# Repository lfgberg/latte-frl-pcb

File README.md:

# This has not yet been tested, and firmware has not yet been pushed to qmk/via, pcb may or may not function as intended

# Latte FRL PCB

PCB designed for Keyboard Cafe's Latte FRL WKL TKL keyboard. PCB art by the wonderful [Stellaidescope](https://twitter.com/stellaidoscope).

## Renders

## Layout

## Production

Download the [latest release of the production files](https://github.com/lfgberg/latte-frl-pcb/releases), and submit them to a PCB manufacturer like JLCPCB or PCBWay.

## Author
[Lfgberg](https://github.com/lfgberg)
<br>

## License
[Attribution-NonCommercial-ShareAlike 4.0 International](https://creativecommons.org/licenses/by-nc-sa/4.0/)

This is not available for commercial use, contact [Lfgberg](https://github.com/lfgberg) for more information.

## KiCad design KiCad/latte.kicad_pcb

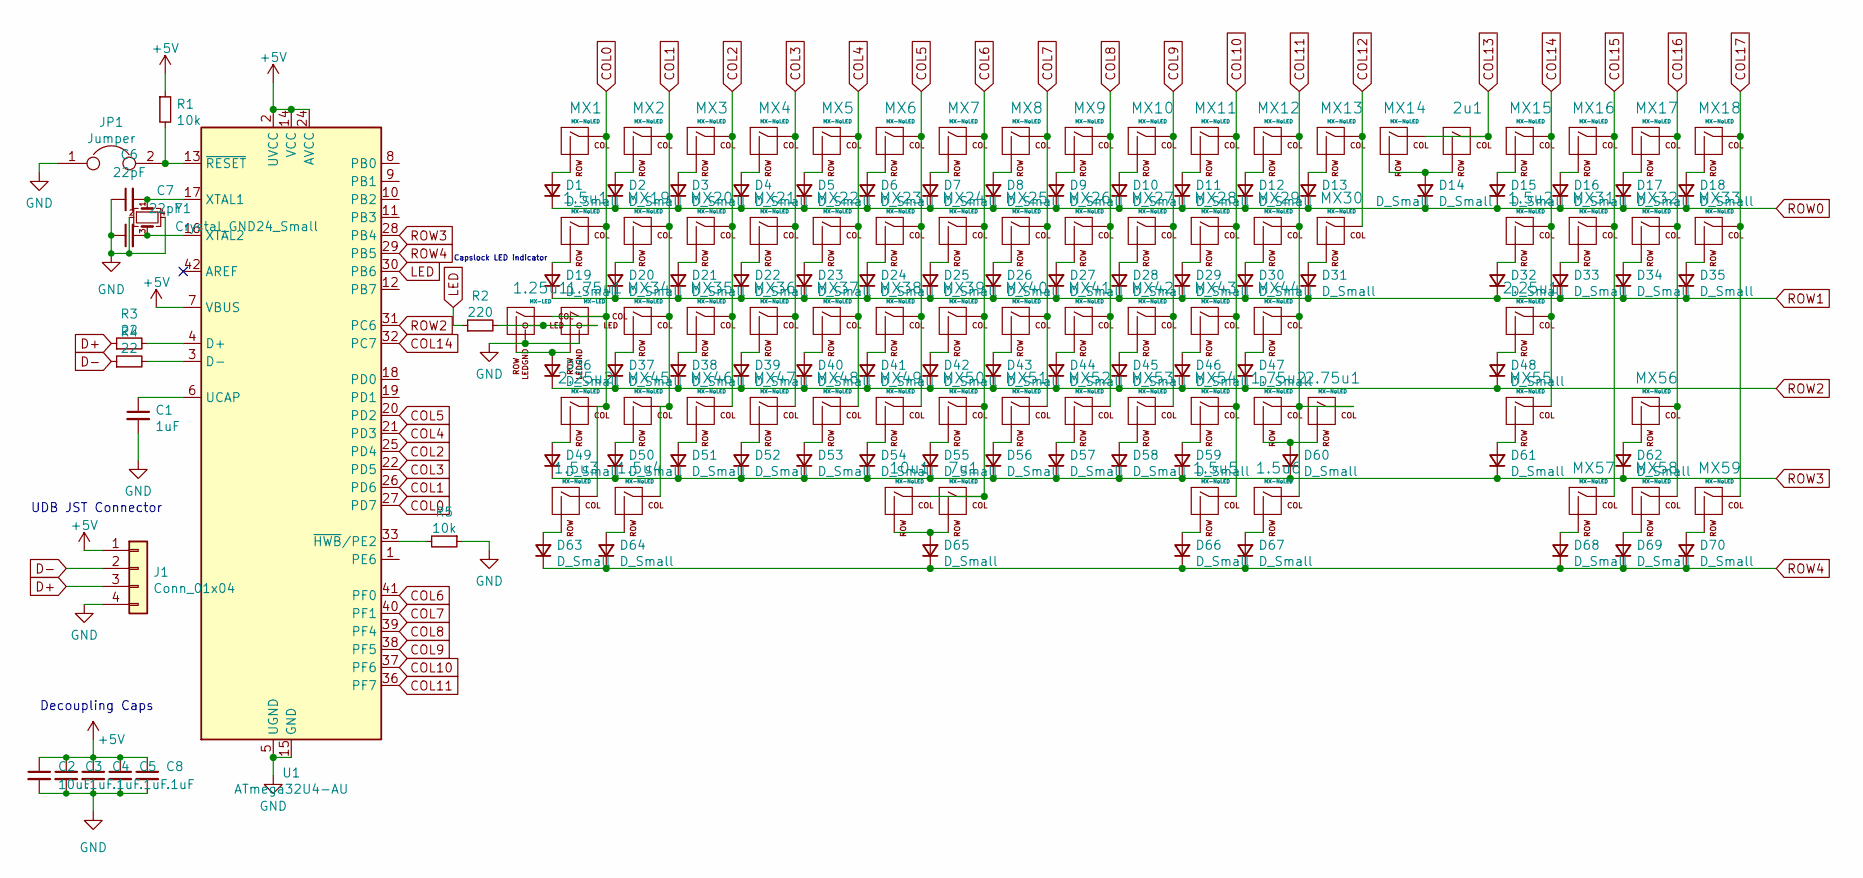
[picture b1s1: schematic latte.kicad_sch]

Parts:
1.5u1, 1.5u2, 1.5u3, 1.5u4, 1.5u5, 1.5u6: MX-NoLED; MXOnly-1.5U-NoLED
1.25u1: MX-LED; MXOnly-1.25U
1.75u1: MX-LED; MXOnly-1.75U
1.75u2: MX-NoLED; MXOnly-1.75U-NoLED
2.25u1, 2.25u2: MX-NoLED; MXOnly-2.25U-NoLED
2.75u1: MX-NoLED; MXOnly-2.75U-NoLED
2u1: MXOnly-2U-NoLED
7u1: MX-NoLED; MXOnly-7U-ReversedStabilizers-NoLED
10u1: MX-NoLED; MX-8U-NoSwitch
C1: 1uF; C_0805_2012Metric
C2: 10uF; C_0805_2012Metric
C3, C4, C5, C8: .1uF; C_0805_2012Metric
C6, C7: 22pF; C_0805_2012Metric
D1, D2, D3, D4, D5, D6, D7, D8, D9, D10, D11, D12, D13, D14, D15, D16, D17, D18, D19, D20, D21, D22, D23, D24, D25, D26, D27, D28, D29, D30, D31, D32, D33, D34, D35, D36, D37, D38, D39, D40, D41, D42, D43, D44, D45, D46, D47, D48, D49, D50, D51, D52, D53, D54, D55, D56, D57, D58, D59, D60, D61, D62, D63, D64, D65, D66, D67, D68, D69, D70: D_Small; D_SOD-123-Pretty
J1: Conn_01x04; JST-SR-4
JP1: Jumper; ResetJumper
MX1, MX2, MX3, MX4, MX5, MX6, MX7, MX8, MX9, MX10, MX11, MX12, MX13, MX14, MX15, MX16, MX17, MX18, MX19, MX20, MX21, MX22, MX23, MX24, MX25, MX26, MX27, MX28, MX29, MX30, MX31, MX32, MX33, MX34, MX35, MX36, MX37, MX38, MX39, MX40, MX41, MX42, MX43, MX44, MX45, MX46, MX47, MX48, MX49, MX50, MX51, MX52, MX53, MX54, MX55, MX56, MX57, MX58, MX59: MX-NoLED; MXOnly-1U-NoLED
R1, R5: 10k; R_0805_2012Metric
R2: 220; R_0805_2012Metric
R3, R4: 22; R_0805_2012Metric
U1: ATmega32U4-AU; QFN_TQFP-44_Combined
Y1: Crystal_GND24_Small; Crystal_SMD_3225-4Pin_3.2x2.5mm_HandSoldering

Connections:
+5V: C2.1, C3.1, C4.1, C5.1, C8.1, J1.1, R1.1, U1.2 (UVCC), U1.7 (VBUS), U1.14 (VCC), U1.24 (AVCC), U1.34 (VCC), U1.44 (AVCC)
COL0: 1.5u1.1 (COL), 1.5u3.1 (COL), 1.25u1.1 (COL), 1.75u1.1 (COL), 2.25u2.1 (COL), MX1.1 (COL), U1.27 (PD7)
COL1: 1.5u4.1 (COL), MX2.1 (COL), MX19.1 (COL), MX34.1 (COL), MX45.1 (COL), U1.26 (PD6)
COL2: MX3.1 (COL), MX20.1 (COL), MX35.1 (COL), MX46.1 (COL), U1.25 (PD4)
COL3: MX4.1 (COL), MX21.1 (COL), MX36.1 (COL), MX47.1 (COL), U1.22 (PD5)
COL4: MX5.1 (COL), MX22.1 (COL), MX37.1 (COL), MX48.1 (COL), U1.21 (PD3)
COL5: MX6.1 (COL), MX23.1 (COL), MX38.1 (COL), MX49.1 (COL), U1.20 (PD2)
COL6: 7u1.1 (COL), 10u1.1 (COL), MX7.1 (COL), MX24.1 (COL), MX39.1 (COL), MX50.1 (COL), U1.41 (PF0)
COL7: MX8.1 (COL), MX25.1 (COL), MX40.1 (COL), MX51.1 (COL), U1.40 (PF1)
COL8: MX9.1 (COL), MX26.1 (COL), MX41.1 (COL), MX52.1 (COL), U1.39 (PF4)
COL9: MX10.1 (COL), MX27.1 (COL), MX42.1 (COL), MX53.1 (COL), U1.38 (PF5)
COL10: 1.5u5.1 (COL), MX11.1 (COL), MX28.1 (COL), MX43.1 (COL), MX54.1 (COL), U1.37 (PF6)
COL11: 1.5u6.1 (COL), 1.75u2.1 (COL), 2.75u1.1 (COL), MX12.1 (COL), MX29.1 (COL), MX44.1 (COL), U1.36 (PF7)
COL12: MX13.1 (COL), MX30.1 (COL)
COL13: 2u1.1 (COL), MX14.1 (COL)
COL14: 1.5u2.1 (COL), 2.25u1.1 (COL), MX15.1 (COL), MX55.1 (COL), U1.32 (PC7)
COL15: MX16.1 (COL), MX31.1 (COL), MX57.1 (COL)
COL16: MX17.1 (COL), MX32.1 (COL), MX56.1 (COL), MX58.1 (COL)
COL17: MX18.1 (COL), MX33.1 (COL), MX59.1 (COL)
D+: J1.3, R3.1
D-: J1.2, R4.1
GND: 1.25u1.4 (LEDGND), 1.75u1.4 (LEDGND), C1.2, C2.2, C3.2, C4.2, C5.2, C6.1, C7.1, C8.2, J1.4, JP1.1, R5.1, U1.5 (UGND), U1.15 (GND), U1.23 (GND), U1.35 (GND), U1.43 (GND), Y1.2, Y1.4
LED: R2.1, U1.30 (PB6)
unnamed: 1.5u1.2 (ROW), D19.2 (A)
unnamed: 1.5u2.2 (ROW), D32.2 (A)
unnamed: 1.5u3.2 (ROW), D63.2 (A)
unnamed: 1.5u4.2 (ROW), D64.2 (A)
unnamed: 1.5u5.2 (ROW), D66.2 (A)
unnamed: 1.5u6.2 (ROW), D67.2 (A)
unnamed: 1.25u1.2 (ROW), 1.75u1.2 (ROW), D36.2 (A)
unnamed: 1.25u1.3 (LED), 1.75u1.3 (LED), R2.2
unnamed: 1.75u2.2 (ROW), 2.75u1.2 (ROW), D60.2 (A)
unnamed: 2.25u1.2 (ROW), D48.2 (A)
unnamed: 2.25u2.2 (ROW), D49.2 (A)
unnamed: 2u1.2 (ROW), D14.2 (A), MX14.2 (ROW)
unnamed: 7u1.2 (ROW), 10u1.2 (ROW), D65.2 (A)
unnamed: C1.1, U1.6 (UCAP)
unnamed: C6.2, U1.17 (XTAL1), Y1.1
unnamed: C7.2, U1.16 (XTAL2), Y1.3
unnamed: D1.2 (A), MX1.2 (ROW)
unnamed: D2.2 (A), MX2.2 (ROW)
unnamed: D3.2 (A), MX3.2 (ROW)
unnamed: D4.2 (A), MX4.2 (ROW)
unnamed: D5.2 (A), MX5.2 (ROW)
unnamed: D6.2 (A), MX6.2 (ROW)
unnamed: D7.2 (A), MX7.2 (ROW)
unnamed: D8.2 (A), MX8.2 (ROW)
unnamed: D9.2 (A), MX9.2 (ROW)
unnamed: D10.2 (A), MX10.2 (ROW)
unnamed: D11.2 (A), MX11.2 (ROW)
unnamed: D12.2 (A), MX12.2 (ROW)
unnamed: D13.2 (A), MX13.2 (ROW)
unnamed: D15.2 (A), MX15.2 (ROW)
unnamed: D16.2 (A), MX16.2 (ROW)
unnamed: D17.2 (A), MX17.2 (ROW)
unnamed: D18.2 (A), MX18.2 (ROW)
unnamed: D20.2 (A), MX19.2 (ROW)
unnamed: D21.2 (A), MX20.2 (ROW)
unnamed: D22.2 (A), MX21.2 (ROW)
unnamed: D23.2 (A), MX22.2 (ROW)
unnamed: D24.2 (A), MX23.2 (ROW)
unnamed: D25.2 (A), MX24.2 (ROW)
unnamed: D26.2 (A), MX25.2 (ROW)
unnamed: D27.2 (A), MX26.2 (ROW)
unnamed: D28.2 (A), MX27.2 (ROW)
unnamed: D29.2 (A), MX28.2 (ROW)
unnamed: D30.2 (A), MX29.2 (ROW)
unnamed: D31.2 (A), MX30.2 (ROW)
unnamed: D33.2 (A), MX31.2 (ROW)
unnamed: D34.2 (A), MX32.2 (ROW)
unnamed: D35.2 (A), MX33.2 (ROW)
unnamed: D37.2 (A), MX34.2 (ROW)
unnamed: D38.2 (A), MX35.2 (ROW)
unnamed: D39.2 (A), MX36.2 (ROW)
unnamed: D40.2 (A), MX37.2 (ROW)
unnamed: D41.2 (A), MX38.2 (ROW)
unnamed: D42.2 (A), MX39.2 (ROW)
unnamed: D43.2 (A), MX40.2 (ROW)
unnamed: D44.2 (A), MX41.2 (ROW)
unnamed: D45.2 (A), MX42.2 (ROW)
unnamed: D46.2 (A), MX43.2 (ROW)
unnamed: D47.2 (A), MX44.2 (ROW)
unnamed: D50.2 (A), MX45.2 (ROW)
unnamed: D51.2 (A), MX46.2 (ROW)
unnamed: D52.2 (A), MX47.2 (ROW)
unnamed: D53.2 (A), MX48.2 (ROW)
unnamed: D54.2 (A), MX49.2 (ROW)
unnamed: D55.2 (A), MX50.2 (ROW)
unnamed: D56.2 (A), MX51.2 (ROW)
unnamed: D57.2 (A), MX52.2 (ROW)
unnamed: D58.2 (A), MX53.2 (ROW)
unnamed: D59.2 (A), MX54.2 (ROW)
unnamed: D61.2 (A), MX55.2 (ROW)
unnamed: D62.2 (A), MX56.2 (ROW)
unnamed: D68.2 (A), MX57.2 (ROW)
unnamed: D69.2 (A), MX58.2 (ROW)
unnamed: D70.2 (A), MX59.2 (ROW)
unnamed: JP1.2, R1.2, U1.13 (~RESET)
unnamed: R3.2, U1.4 (D+)
unnamed: R4.2, U1.3 (D-)
unnamed: R5.2, U1.33 (~HWB/PE2)
ROW0: D1.1 (K), D2.1 (K), D3.1 (K), D4.1 (K), D5.1 (K), D6.1 (K), D7.1 (K), D8.1 (K), D9.1 (K), D10.1 (K), D11.1 (K), D12.1 (K), D13.1 (K), D14.1 (K), D15.1 (K), D16.1 (K), D17.1 (K), D18.1 (K)
ROW1: D19.1 (K), D20.1 (K), D21.1 (K), D22.1 (K), D23.1 (K), D24.1 (K), D25.1 (K), D26.1 (K), D27.1 (K), D28.1 (K), D29.1 (K), D30.1 (K), D31.1 (K), D32.1 (K), D33.1 (K), D34.1 (K), D35.1 (K)
ROW2: D36.1 (K), D37.1 (K), D38.1 (K), D39.1 (K), D40.1 (K), D41.1 (K), D42.1 (K), D43.1 (K), D44.1 (K), D45.1 (K), D46.1 (K), D47.1 (K), D48.1 (K), U1.31 (PC6)
ROW3: D49.1 (K), D50.1 (K), D51.1 (K), D52.1 (K), D53.1 (K), D54.1 (K), D55.1 (K), D56.1 (K), D57.1 (K), D58.1 (K), D59.1 (K), D60.1 (K), D61.1 (K), D62.1 (K), U1.28 (PB4)
ROW4: D63.1 (K), D64.1 (K), D65.1 (K), D66.1 (K), D67.1 (K), D68.1 (K), D69.1 (K), D70.1 (K), U1.29 (PB5)

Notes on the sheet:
UDB JST Connector
Decoupling Caps
Capslock LED indicator

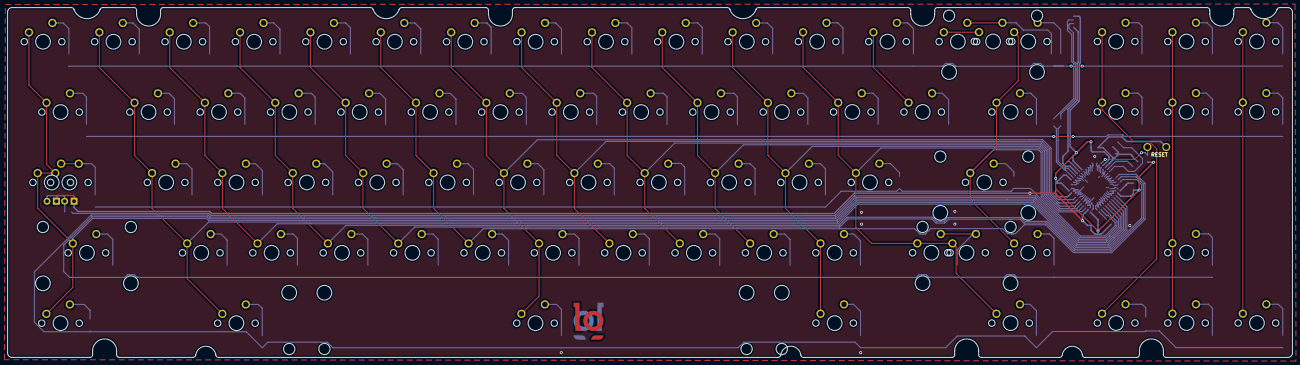
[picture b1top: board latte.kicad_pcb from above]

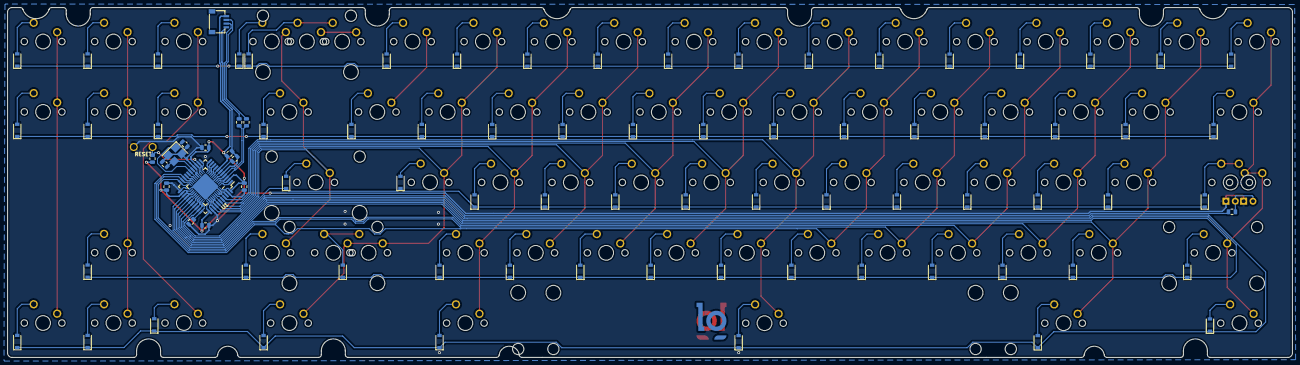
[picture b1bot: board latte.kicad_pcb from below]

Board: 2 copper layers, 347.8 x 94.7 mm, 161 parts (87 on the bottom side), 106 nets.

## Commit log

2021-04-05 started
    started
2021-07-17 placed components
2021-09-26 honestly bro i forget what i did here
2021-10-21 finish v1
2021-10-22 Update README.MD
    - add images
2021-10-22 add latte.STEP
2021-10-22 add production files
2021-10-27 v1.1
    -add sera silk
    -add lg branding
    - add new images
2023-02-16 add buymeacoffee
